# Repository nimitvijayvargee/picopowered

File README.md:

# picopowered
A simple microcontroller built around the RP2040.

# Changelog (V3)
- Redesigned board layout
- Doubled headers
- Dip switches and SD card slot connected to GP13-15 and GP16-19+29 respectively
- Better power system and circuit design

# Changelog (V2)
- Replaced 2020 Neopixel with more available 5050 footprint.
- Fixed seperation between 1v1 and 3v3 power planes.
- Better positioning and tracing of the components to improve overall signal integrity.
- Added a regular LED to keep it somewhat compatible with regular Pico SDK Code.
- Modified USB C port to be THT Mounted rather than completely SMD.
- Moved GPIO 29 from VSYS Sense to an exposed pad on the bottom side of the PCB.

# Featureset
| **Stat**         | **Raspberry Pi Pico 1** | **Picopowered V1-RP2040** |
|------------------|-------------------------|---------------------------|
| Flash            | 2MB                     | 16MB                      |
| Reset Button     | No                      | Yes                       |
| LED              | Yes (1 Color)           | Yes (RGB Neopixel)        |
| User GPIO Button | No                      | Yes                       |
| USB Type         | Micro-B                 | C                         |

# Disadvantages
- Linear regulator requuires minimum of 3.3 Volts, unlike Pico's buck boost converter which can be powered by 1.8 Volts.
- ~~No ADC_VREF (connected to GND instead) because the power by linear regulator is filtered already.~~ ADC VREF now works with picopowered V2 and V3
- No Power Mode selection (stems from power supply used)

Most of the disadvantages occur only due to the Pico's superior power supply system, but the system on the PicoPowered board is more filtered and smooth.

# BOM
| **Part**         | **Cost (USD)**          |
|------------------|-------------------------|
| PCB + Assembly   | 120                     |
| Solder Wire      | 3                       |
| Headers          | 3                       |

For parts specific BOM, check picopowered.csv in /Production/

# Gallery
## V3 (Latest)

## V2

## V1

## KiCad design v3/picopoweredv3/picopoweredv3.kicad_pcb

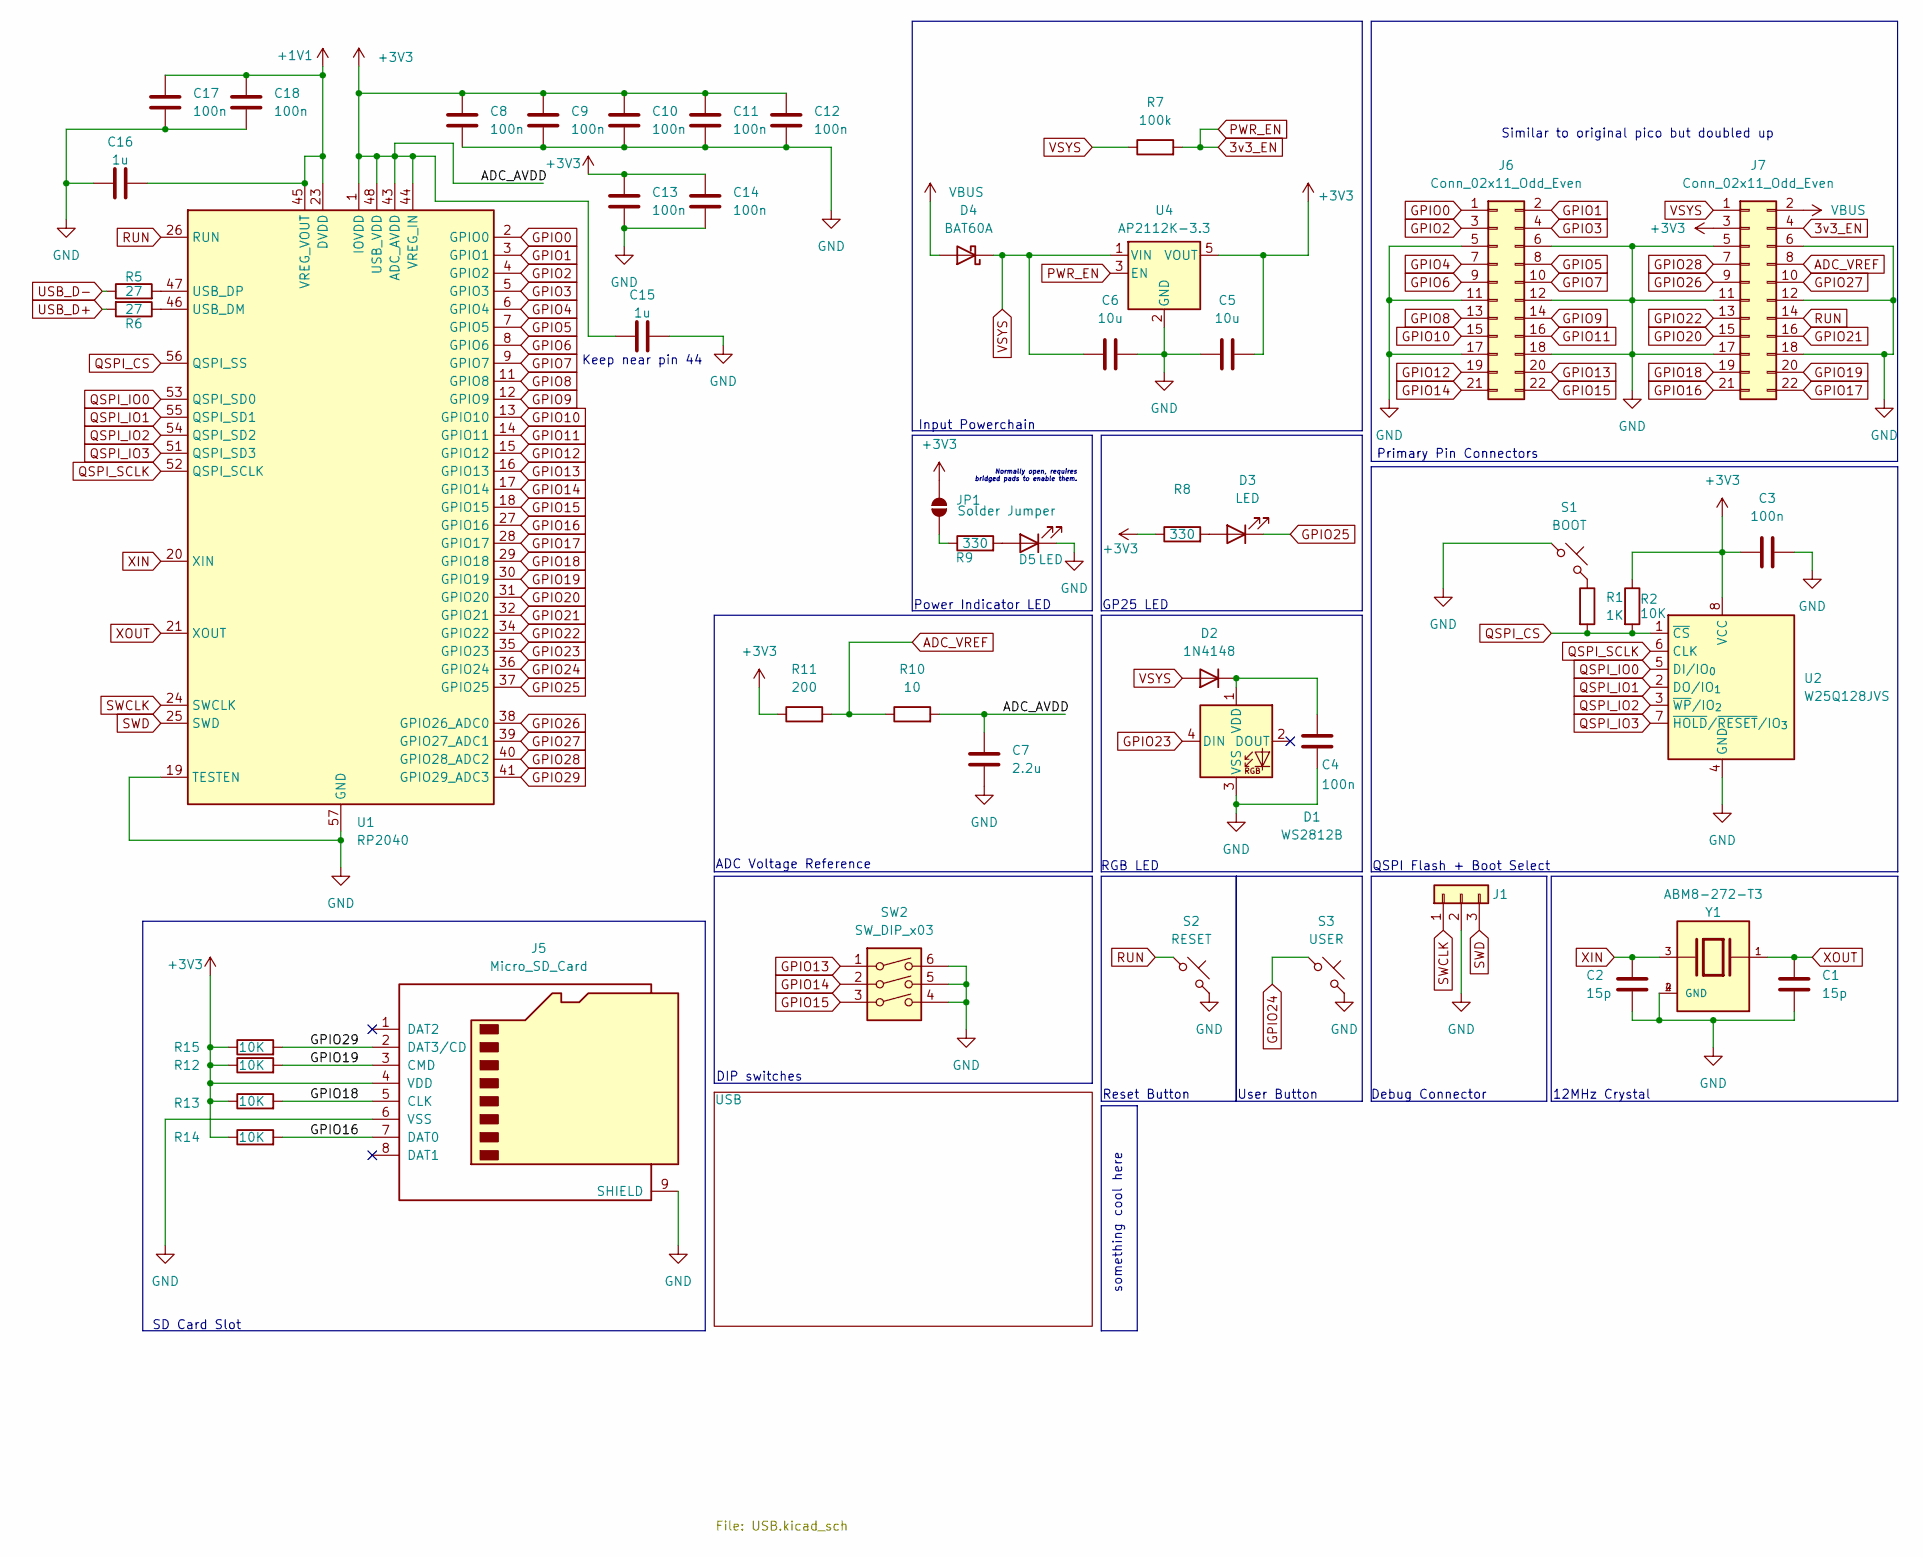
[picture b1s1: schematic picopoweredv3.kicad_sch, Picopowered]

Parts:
C1, C2: 15p; C_0402_1005Metric
C3, C4, C8, C9, C10, C11, C12, C13, C14, C17, C18: 100n; C_0402_1005Metric
C5, C6: 10u; C_0402_1005Metric
C7: 2.2u; C_0402_1005Metric
C15, C16: 1u; C_0402_1005Metric
D1: WS2812B; LED_WS2812B_PLCC4_5.0x5.0mm_P3.2mm
D2: 1N4148; D_SOD-123
D3, D5: LED; LED_0603_1608Metric
D4: BAT60A; D_SOD-323
J1: Conn_01x03; PinHeader_1x03_P2.54mm_Vertical
J5: Micro_SD_Card; Micro_SD_READER
J6, J7: Conn_02x11_Odd_Even; PinHeader_2x11_P2.54mm_Vertical
JP1: Solder Jumper; SolderJumper-2_P1.3mm_Open_TrianglePad1.0x1.5mm
R1: 1K; R_0402_1005Metric
R2, R12, R13, R14, R15: 10K; R_0402_1005Metric
R5, R6: 27; R_0402_1005Metric
R7: 100k; R_0402_1005Metric
R8, R9: 330; R_0402_1005Metric
R10: 10; R_0402_1005Metric
R11: 200; R_0402_1005Metric
S1: BOOT; SW_SPST_B3U-1000P
S2: RESET; SW_SPST_B3U-1000P
S3: USER; SW_SPST_B3U-1000P
SW2: SW_DIP_x03; SW_DIP_SPSTx03_Slide_6.7x9.18mm_W7.62mm_P2.54mm_LowProfile
U1: RP2040; QFN-56-1EP_7x7mm_P0.4mm_EP3.2x3.2mm
U2: W25Q128JVS; SOIC-8_5.3x5.3mm_P1.27mm
U4: AP2112K-3.3; SOT-23-5
Y1: ABM8-272-T3; XTAL_ABM8-272-T3; PARTREV 07-29-20

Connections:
3v3_EN: J7.4, R7.2, U4.3 (EN)
+1V1: C16.1, C17.1, C18.1, U1.23 (DVDD), U1.45 (VREG_VOUT), U1.50 (DVDD)
+3V3: C3.1, C5.1, C7.1, C8.1, C9.1, C10.1, C11.1, C12.1, C13.1, C14.1, C15.1, J5.4 (VDD), J7.3, JP1.2 (B), R2.1, R8.1, R10.2, R11.1, R12.1, R13.1, R14.1, R15.1, U1.1 (IOVDD), U1.10 (IOVDD), U1.22 (IOVDD), U1.33 (IOVDD), U1.42 (IOVDD), U1.43 (ADC_AVDD), U1.44 (VREG_IN), U1.48 (USB_VDD), U1.49 (IOVDD), U2.8 (VCC), U4.5 (VOUT)
ADC_VREF: J7.8, R10.1, R11.2
GND: C1.2, C2.2, C3.2, C4.1, C5.2, C6.2, C7.2, C8.2, C9.2, C10.2, C11.2, C12.2, C13.2, C14.2, C15.2, C16.2, C17.2, C18.2, D1.3 (VSS), D5.1 (K), J1.2, J5.6 (VSS), J5.9 (SHIELD), J6.5, J6.6, J6.11, J6.12, J6.17, J6.18, J7.5, J7.6, J7.11, J7.12, J7.17, J7.18, S1.1, S2.2, S3.2, SW2.4, SW2.5, SW2.6, U1.19 (TESTEN), U1.57 (GND), U2.4 (GND), U4.2 (GND), Y1.2 (GND), Y1.4 (GND); also elsewhere on the board
GPIO0: J6.1, U1.2 (GPIO0)
GPIO1: J6.2, U1.3 (GPIO1)
GPIO2: J6.3, U1.4 (GPIO2)
GPIO3: J6.4, U1.5 (GPIO3)
GPIO4: J6.7, U1.6 (GPIO4)
GPIO5: J6.8, U1.7 (GPIO5)
GPIO6: J6.9, U1.8 (GPIO6)
GPIO7: J6.10, U1.9 (GPIO7)
GPIO8: J6.13, U1.11 (GPIO8)
GPIO9: J6.14, U1.12 (GPIO9)
GPIO10: J6.15, U1.13 (GPIO10)
GPIO11: J6.16, U1.14 (GPIO11)
GPIO12: J6.19, U1.15 (GPIO12)
GPIO13: J6.20, SW2.1, U1.16 (GPIO13)
GPIO14: J6.21, SW2.2, U1.17 (GPIO14)
GPIO15: J6.22, SW2.3, U1.18 (GPIO15)
GPIO16: J5.7 (DAT0), J7.21, R14.2, U1.27 (GPIO16)
GPIO17: J7.22, U1.28 (GPIO17)
GPIO18: J5.5 (CLK), J7.19, R13.2, U1.29 (GPIO18)
GPIO19: J5.3 (CMD), J7.20, R12.2, U1.30 (GPIO19)
GPIO20: J7.15, U1.31 (GPIO20)
GPIO21: J7.16, U1.32 (GPIO21)
GPIO22: J7.13, U1.34 (GPIO22)
GPIO23: D1.4 (DIN), U1.35 (GPIO23)
GPIO24: S3.1, U1.36 (GPIO24)
GPIO25: D3.1 (K), U1.37 (GPIO25)
GPIO26: J7.9, U1.38 (GPIO26_ADC0)
GPIO27: J7.10, U1.39 (GPIO27_ADC1)
GPIO28: J7.7, U1.40 (GPIO28_ADC2)
GPIO29: J5.2 (DAT3/CD), R15.2, U1.41 (GPIO29_ADC3)
unnamed: C4.2, D1.1 (VDD), D2.1 (K)
unnamed: D3.2 (A), R8.2
unnamed: D5.2 (A), R9.2
unnamed: JP1.1 (A), R9.1
unnamed: R1.1, S1.2
unnamed: R6.1, U1.46 (USB_DM)
unnamed: R5.2, U1.47 (USB_DP)
QSPI_CS: R1.2, R2.2, U1.56 (QSPI_SS), U2.1 (~CS)
QSPI_IO0: U1.53 (QSPI_SD0), U2.5 (DI/IO_{0})
QSPI_IO1: U1.55 (QSPI_SD1), U2.2 (DO/IO_{1})
QSPI_IO2: U1.54 (QSPI_SD2), U2.3 (~WP/IO_{2})
QSPI_IO3: U1.51 (QSPI_SD3), U2.7 (~HOLD/~RESET/IO_{3})
QSPI_SCLK: U1.52 (QSPI_SCLK), U2.6 (CLK)
RUN: J7.14, S2.1, U1.26 (RUN)
SWCLK: J1.1, U1.24 (SWCLK)
SWD: J1.3, U1.25 (SWD)
USB_D+: R6.2; also elsewhere on the board
USB_D-: R5.1; also elsewhere on the board
VBUS: D4.2 (A), J7.2; also elsewhere on the board
VSYS: C6.1, D2.2 (A), D4.1 (K), J7.1, R7.1, U4.1 (VIN)
XIN: C2.1, U1.20 (XIN), Y1.3
XOUT: C1.1, U1.21 (XOUT), Y1.1

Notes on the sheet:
Similar to original pico but doubled up
DIP switches
ADC Voltage Reference
Normally open, requires bridged pads to enable them.
GP25 LED
User Button
QSPI Flash + Boot Select
Primary Pin Connectors
something cool here
RGB LED
Input Powerchain
Debug Connector
12MHz Crystal
Keep near pin 44
SD Card Slot
Power Indicator LED
Reset Button

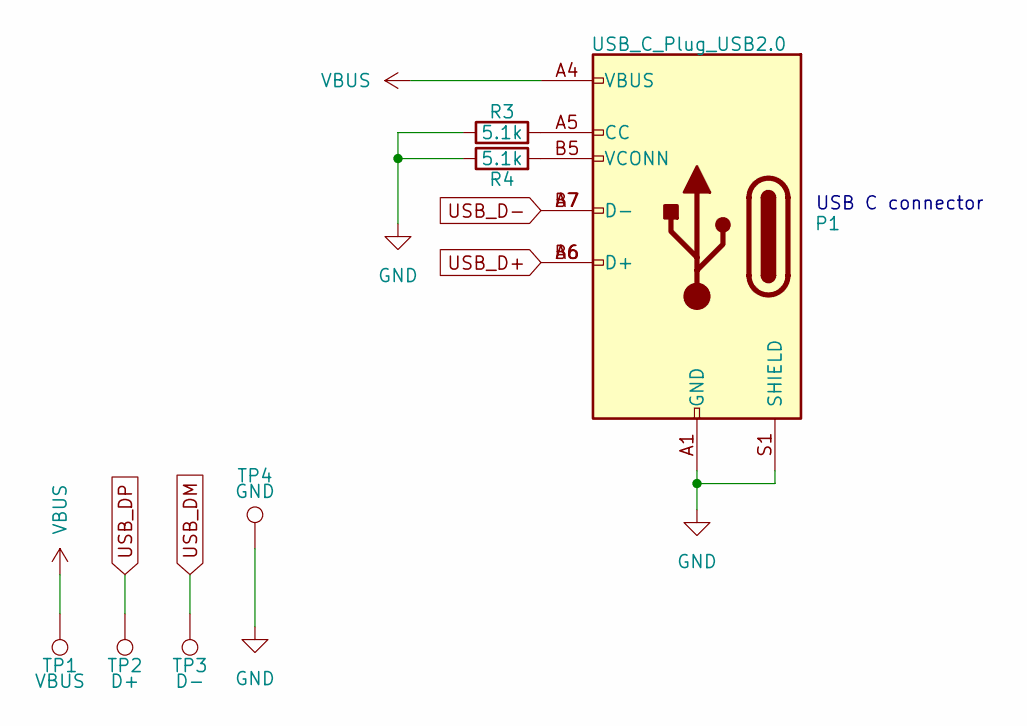
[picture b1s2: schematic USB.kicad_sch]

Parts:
P1: USB_C_Plug_USB2.0; USB_C_Receptacle_GCT_USB4105-xx-A_16P_TopMnt_Horizontal
R3, R4: 5.1k; R_0402_1005Metric
TP1: VBUS; TestPoint_Pad_1.0x1.0mm
TP2: D+; TestPoint_Pad_1.0x1.0mm
TP3: D-; TestPoint_Pad_1.0x1.0mm
TP4: GND; TestPoint_Pad_1.0x1.0mm

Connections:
GND: P1.A1 (GND), P1.A12 (GND), P1.B1 (GND), P1.B12 (GND), P1.S1 (SHIELD), R3.1, R4.1, TP4.1; also elsewhere on the board
unnamed: P1.A5 (CC), R3.2
unnamed: P1.B5 (VCONN), R4.2
USB_D+: P1.A6 (D+), P1.B6 (D+); also elsewhere on the board
USB_D-: P1.A7 (D-), P1.B7 (D-); also elsewhere on the board
VBUS: P1.A4 (VBUS), P1.A9 (VBUS), P1.B4 (VBUS), P1.B9 (VBUS), TP1.1; also elsewhere on the board

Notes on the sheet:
USB C connector

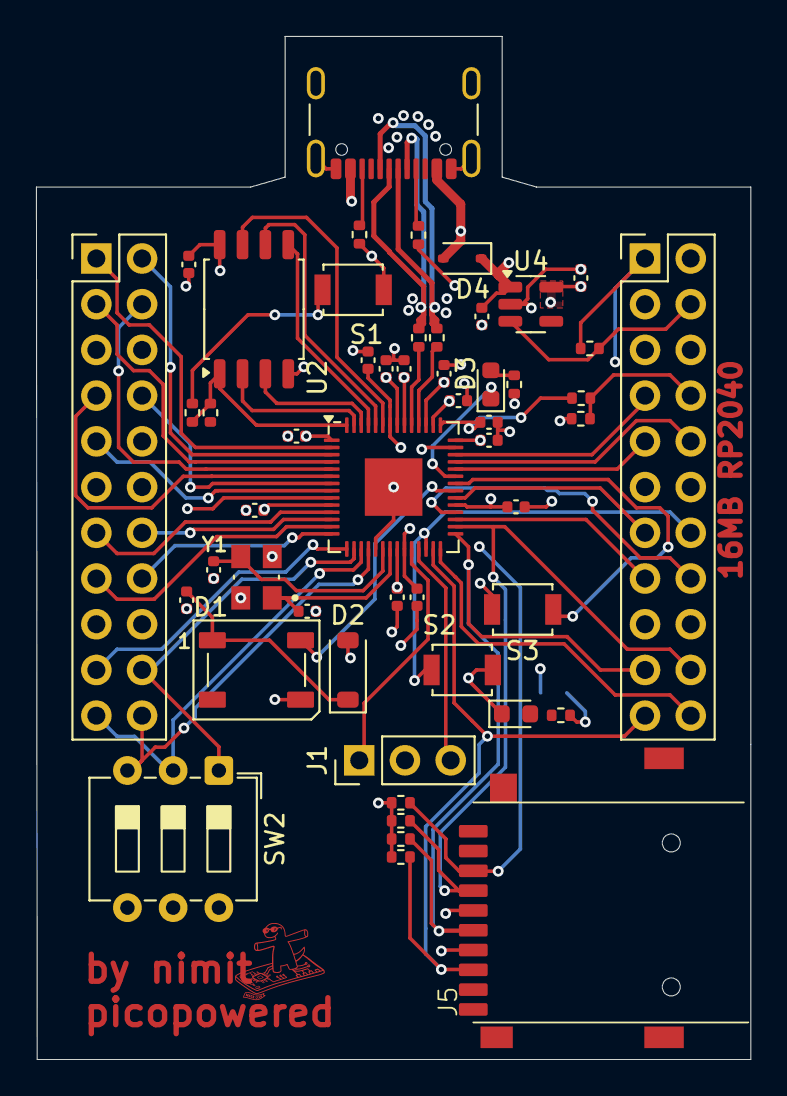
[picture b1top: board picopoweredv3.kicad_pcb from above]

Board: 4 copper layers, 39.7 x 56.8 mm, 52 parts (1 on the bottom side), 59 nets.

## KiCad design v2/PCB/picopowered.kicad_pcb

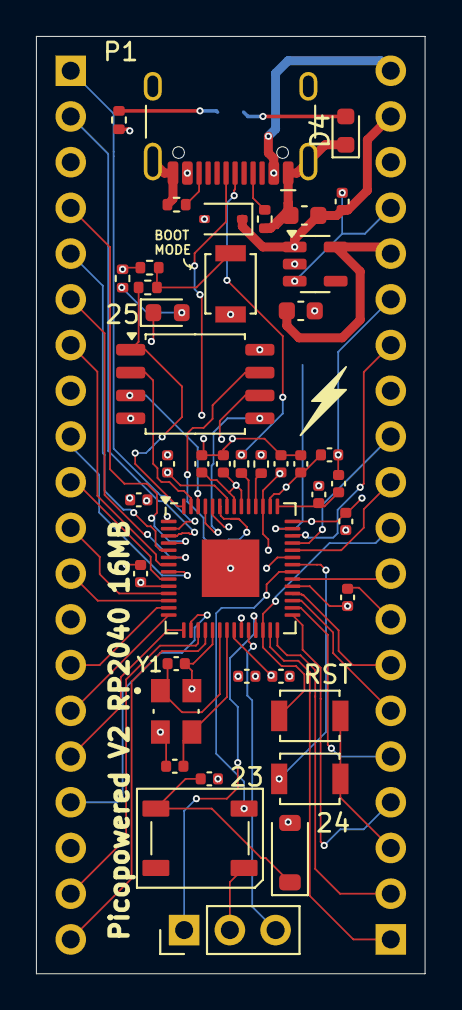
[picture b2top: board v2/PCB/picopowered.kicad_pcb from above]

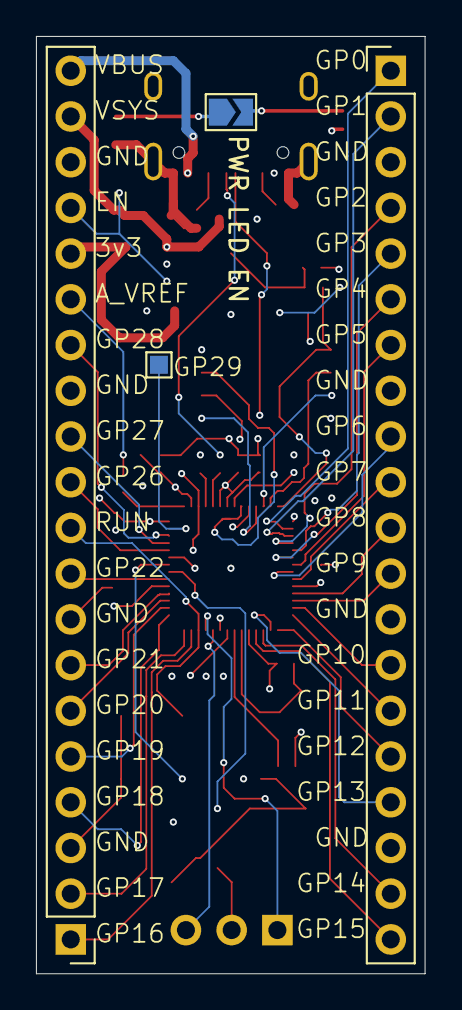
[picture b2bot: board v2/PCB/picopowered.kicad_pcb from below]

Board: 4 copper layers, 21.6 x 52.1 mm, 46 parts (4 on the bottom side), 60 nets.

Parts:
24: USER_BUTTON; SW_SPST_B3U-1000P
25: LED; LED_0603_1608Metric
BOOT: BOOT_SELECT; SW_SPST_B3U-1000P
C1, C2: 15p; C_0402_1005Metric
C3, C4, C5, C6, C7, C8, C9, C10, C10#2, C13: 100n; C_0402_1005Metric
C11, C12, C16: 2.2u; C_0402_1005Metric
C14: 10u; C_0603_1608Metric
C15: 22u; C_0603_1608Metric
D1: WS2812B; LED_WS2812B_PLCC4_5.0x5.0mm_P3.2mm
D2: 1N4148; D_SOD-123
D4: LED; LED_0603_1608Metric
D5: BAT60A; D_SOD-323
J1: Conn_01x03; PinHeader_1x03_P2.54mm_Vertical
J2, J3: Conn_01x20; PinHeader_1x20_P2.54mm_Vertical
P1: USB_C_Plug_USB2.0; USB_C_Receptacle_HCTL_HC-TYPE-C-16P-01A
PWR LED EN: SolderJumper_2_Open; SolderJumper-2_P1.3mm_Open_TrianglePad1.0x1.5mm
Picopowered V2 RP2040 16MB: RP2040; QFN-56-1EP_7x7mm_P0.4mm_EP3.2x3.2mm
R1, R2: 27; R_0402_1005Metric
R3: 1k; R_0402_1005Metric
R4: 10k; R_0402_1005Metric
R5, R6: 5.1k; R_0402_1005Metric
R7, R8: 330; R_0402_1005Metric
R9: 10; C_0402_1005Metric
R10: 200; C_0402_1005Metric
R11: 100K; C_0402_1005Metric
RST: Keyswitch; SW_SPST_B3U-1000P
TP1: GP29; TestPoint_Pad_1.0x1.0mm
U2: W25Q128JVS; SOIC-8_5.3x5.3mm_P1.27mm
U4: AP2112K-3.3; SOT-23-5
Y1: ABM8-272-T3; XTAL_ABM8-272-T3

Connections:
3v3_EN: J3.17, R11.1, U4.3 (EN)
+1V1: C3.1, C4.1, C12.1, Picopowered V2 RP2040 16MB.23 (DVDD), Picopowered V2 RP2040 16MB.45 (VREG_VOUT), Picopowered V2 RP2040 16MB.50 (DVDD)
+3V3: C5.1, C6.1, C7.1, C8.1, C9.1, C10.1, C10#2.1, C11.1, C15.2, J3.16, Picopowered V2 RP2040 16MB.1 (IOVDD), Picopowered V2 RP2040 16MB.10 (IOVDD), Picopowered V2 RP2040 16MB.22 (IOVDD), Picopowered V2 RP2040 16MB.33 (IOVDD), Picopowered V2 RP2040 16MB.42 (IOVDD), Picopowered V2 RP2040 16MB.44 (VREG_IN), Picopowered V2 RP2040 16MB.48 (USB_VDD), Picopowered V2 RP2040 16MB.49 (IOVDD), R4.2, R7.2, R8.2, R10.1, U2.8 (VCC), U4.5 (VOUT)
ADC_AVDD: C16.1, Picopowered V2 RP2040 16MB.43 (ADC_AVDD), R9.2
ADC_VREF: J3.15, R9.1, R10.2
GND: 24.2, BOOT.1, C1.1, C2.1, C3.2, C4.2, C5.2, C6.2, C7.2, C8.2, C9.2, C10.2, C10#2.2, C11.2, C12.2, C13.2, C14.1, C15.1, C16.2, D1.3 (VSS), D4.1 (K), J1.2, J2.3, J2.8, J2.13, J2.18, J3.3, J3.8, J3.13, J3.18, P1.A1 (GND), P1.A12 (GND), P1.B1 (GND), P1.B12 (GND), P1.S1 (SHIELD), Picopowered V2 RP2040 16MB.19 (TESTEN), Picopowered V2 RP2040 16MB.57 (GND), R5.2, R6.2, RST.2, U2.4 (GND), U4.2 (GND), Y1.2 (GND), Y1.4 (GND)
GPIO0: J2.1, Picopowered V2 RP2040 16MB.2 (GPIO0)
GPIO1: J2.2, Picopowered V2 RP2040 16MB.3 (GPIO1)
GPIO2: J2.4, Picopowered V2 RP2040 16MB.4 (GPIO2)
GPIO3: J2.5, Picopowered V2 RP2040 16MB.5 (GPIO3)
GPIO4: J2.6, Picopowered V2 RP2040 16MB.6 (GPIO4)
GPIO5: J2.7, Picopowered V2 RP2040 16MB.7 (GPIO5)
GPIO6: J2.9, Picopowered V2 RP2040 16MB.8 (GPIO6)
GPIO7: J2.10, Picopowered V2 RP2040 16MB.9 (GPIO7)
GPIO8: J2.11, Picopowered V2 RP2040 16MB.11 (GPIO8)
GPIO9: J2.12, Picopowered V2 RP2040 16MB.12 (GPIO9)
GPIO10: J2.14, Picopowered V2 RP2040 16MB.13 (GPIO10)
GPIO11: J2.15, Picopowered V2 RP2040 16MB.14 (GPIO11)
GPIO12: J2.16, Picopowered V2 RP2040 16MB.15 (GPIO12)
GPIO13: J2.17, Picopowered V2 RP2040 16MB.16 (GPIO13)
GPIO14: J2.19, Picopowered V2 RP2040 16MB.17 (GPIO14)
GPIO15: J2.20, Picopowered V2 RP2040 16MB.18 (GPIO15)
GPIO16: J3.1, Picopowered V2 RP2040 16MB.27 (GPIO16)
GPIO17: J3.2, Picopowered V2 RP2040 16MB.28 (GPIO17)
GPIO18: J3.4, Picopowered V2 RP2040 16MB.29 (GPIO18)
GPIO19: J3.5, Picopowered V2 RP2040 16MB.30 (GPIO19)
GPIO20: J3.6, Picopowered V2 RP2040 16MB.31 (GPIO20)
GPIO21: J3.7, Picopowered V2 RP2040 16MB.32 (GPIO21)
GPIO22: J3.9, Picopowered V2 RP2040 16MB.34 (GPIO22)
GPIO23: D1.4 (DIN), Picopowered V2 RP2040 16MB.35 (GPIO23)
GPIO24: 24.1, Picopowered V2 RP2040 16MB.36 (GPIO24)
GPIO25: 25.1 (K), Picopowered V2 RP2040 16MB.37 (GPIO25)
GPIO26: J3.11, Picopowered V2 RP2040 16MB.38 (GPIO26_ADC0)
GPIO27: J3.12, Picopowered V2 RP2040 16MB.39 (GPIO27_ADC1)
GPIO28: J3.14, Picopowered V2 RP2040 16MB.40 (GPIO28_ADC2)
GPIO29: Picopowered V2 RP2040 16MB.41 (GPIO29_ADC3), TP1.1
unnamed: C13.1, D1.1 (VDD), D2.1 (K)
unnamed: 25.2 (A), R7.1
unnamed: D4.2 (A), PWR LED EN.1 (A)
unnamed: J1.1, Picopowered V2 RP2040 16MB.25 (SWD)
unnamed: J1.3, Picopowered V2 RP2040 16MB.24 (SWCLK)
unnamed: PWR LED EN.2 (B), R8.1
unnamed: P1.A5 (CC), R5.1
unnamed: P1.B5 (VCONN), R6.1
unnamed: BOOT.2, R3.1, R4.1
unnamed: Picopowered V2 RP2040 16MB.46 (USB_DM), R2.2
unnamed: Picopowered V2 RP2040 16MB.47 (USB_DP), R1.2
unnamed: C1.2, Picopowered V2 RP2040 16MB.20 (XIN), Y1.1
unnamed: C2.2, Picopowered V2 RP2040 16MB.21 (XOUT), Y1.3
QSPI_SCLK: Picopowered V2 RP2040 16MB.52 (QSPI_SCLK), U2.6 (CLK)
QSPI_SD0: Picopowered V2 RP2040 16MB.53 (QSPI_SD0), U2.5 (DI/IO_{0})
QSPI_SD1: Picopowered V2 RP2040 16MB.55 (QSPI_SD1), U2.2 (DO/IO_{1})
QSPI_SD2: Picopowered V2 RP2040 16MB.54 (QSPI_SD2), U2.3 (~WP/IO_{2})
QSPI_SD3: Picopowered V2 RP2040 16MB.51 (QSPI_SD3), U2.7 (~HOLD/~RESET/IO_{3})
QSPI_SS: Picopowered V2 RP2040 16MB.56 (QSPI_SS), R3.2, U2.1 (~CS)
RUN: J3.10, Picopowered V2 RP2040 16MB.26 (RUN), RST.1
USB_D+: P1.A6 (D+), R1.1
USB_D-: P1.A7 (D-), R2.1
VBUS: D5.2 (A), J3.20, P1.A4 (VBUS), P1.A9 (VBUS), P1.B4 (VBUS), P1.B9 (VBUS)
VSYS: C14.2, D2.2 (A), D5.1 (K), J3.19, R11.2, U4.1 (VIN)

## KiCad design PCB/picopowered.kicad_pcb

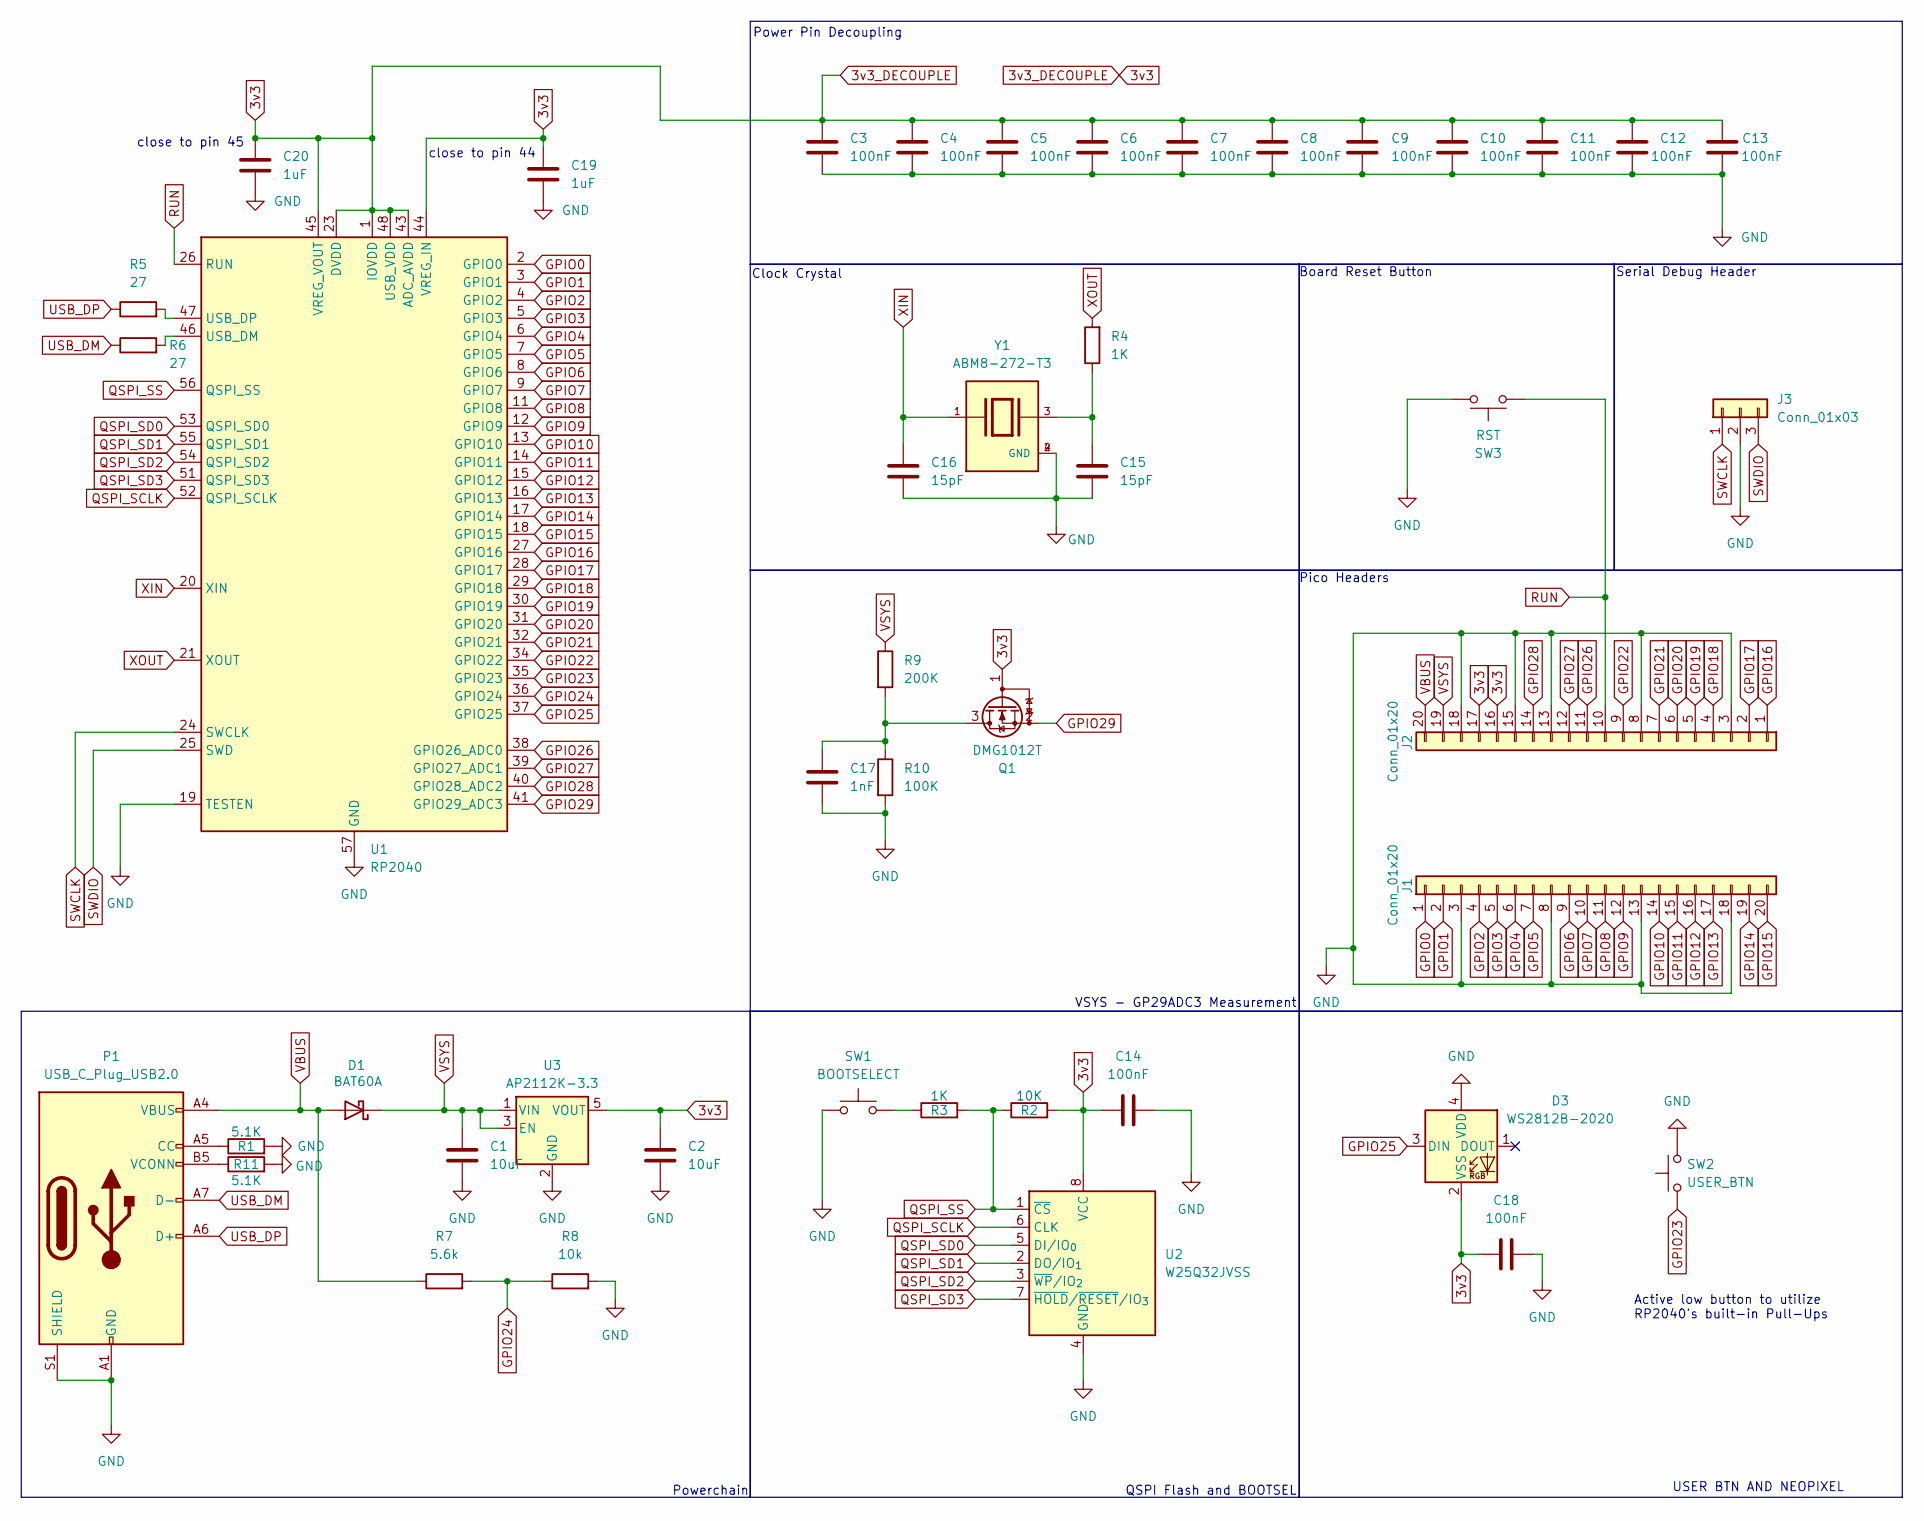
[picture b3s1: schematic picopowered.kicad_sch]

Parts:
C1, C2: 10uF; C_0402_1005Metric
C3, C4, C5, C6, C7, C8, C9, C10, C11, C12, C13, C14, C18: 100nF; C_0402_1005Metric
C15, C16: 15pF; C_0402_1005Metric
C17: 1nF; C_0402_1005Metric
C19, C20: 1uF; C_0402_1005Metric
D1: BAT60A; D_SOD-123
D3: WS2812B-2020; LED_WS2812B-2020_PLCC4_2.0x2.0mm
J1, J2: Conn_01x20; PinHeader_1x20_P2.54mm_Vertical
J3: Conn_01x03; PinHeader_1x03_P2.54mm_Vertical
P1: USB_C_Plug_USB2.0; USB_C_Receptacle_GCT_USB4110
Q1: DMG1012T; SOT-523
R1, R11: 5.1K; R_0402_1005Metric
R2: 10K; R_0402_1005Metric
R3, R4: 1K; R_0402_1005Metric
R5, R6: 27; R_0402_1005Metric
R7: 5.6k; R_0402_1005Metric
R8: 10k; R_0402_1005Metric
R9: 200K; R_0402_1005Metric
R10: 100K; R_0402_1005Metric
SW1: BOOTSELECT; SW_SPST_B3U-1000P
SW2: USER_BTN; SW_SPST_B3U-1000P
SW3: RST; SW_SPST_B3U-1000P
U1: RP2040; QFN-56-1EP_7x7mm_P0.4mm_EP3.2x3.2mm
U2: W25Q32JVSS; SOIC-8_5.3x5.3mm_P1.27mm
U3: AP2112K-3.3; SOT-23-5
Y1: ABM8-272-T3; Crystal_SMD_Abracon_ABM8G-4Pin_3.2x2.5mm; PARTREV 07-29-20

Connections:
3v3: C2.1, C3.1, C4.1, C5.1, C6.1, C7.1, C8.1, C9.1, C10.1, C11.1, C12.1, C13.1, C14.1, C18.1, C19.1, C20.1, D3.2 (VSS), J2.16, J2.17, Q1.1 (G), R2.2, U1.1 (IOVDD), U1.10 (IOVDD), U1.22 (IOVDD), U1.23 (DVDD), U1.33 (IOVDD), U1.42 (IOVDD), U1.43 (ADC_AVDD), U1.44 (VREG_IN), U1.45 (VREG_VOUT), U1.48 (USB_VDD), U1.49 (IOVDD), U1.50 (DVDD), U2.8 (VCC), U3.5 (VOUT)
GND: C1.2, C2.2, C3.2, C4.2, C5.2, C6.2, C7.2, C8.2, C9.2, C10.2, C11.2, C12.2, C13.2, C14.2, C15.1, C16.1, C17.2, C18.2, C19.2, C20.2, D3.4 (VDD), J1.3, J1.8, J1.13, J1.18, J2.3, J2.8, J2.13, J2.15, J2.18, J3.2, P1.A1 (GND), P1.A12 (GND), P1.B1 (GND), P1.B12 (GND), P1.S1 (SHIELD), R1.2, R8.2, R10.2, R11.2, SW1.1, SW2.2, SW3.1, U1.19 (TESTEN), U1.57 (GND), U2.4 (GND), U3.2 (GND), Y1.2 (GND), Y1.4 (GND)
GPIO0: J1.1, U1.2 (GPIO0)
GPIO1: J1.2, U1.3 (GPIO1)
GPIO2: J1.4, U1.4 (GPIO2)
GPIO3: J1.5, U1.5 (GPIO3)
GPIO4: J1.6, U1.6 (GPIO4)
GPIO5: J1.7, U1.7 (GPIO5)
GPIO6: J1.9, U1.8 (GPIO6)
GPIO7: J1.10, U1.9 (GPIO7)
GPIO8: J1.11, U1.11 (GPIO8)
GPIO9: J1.12, U1.12 (GPIO9)
GPIO10: J1.14, U1.13 (GPIO10)
GPIO11: J1.15, U1.14 (GPIO11)
GPIO12: J1.16, U1.15 (GPIO12)
GPIO13: J1.17, U1.16 (GPIO13)
GPIO14: J1.19, U1.17 (GPIO14)
GPIO15: J1.20, U1.18 (GPIO15)
GPIO16: J2.1, U1.27 (GPIO16)
GPIO17: J2.2, U1.28 (GPIO17)
GPIO18: J2.4, U1.29 (GPIO18)
GPIO19: J2.5, U1.30 (GPIO19)
GPIO20: J2.6, U1.31 (GPIO20)
GPIO21: J2.7, U1.32 (GPIO21)
GPIO22: J2.9, U1.34 (GPIO22)
GPIO23: SW2.1, U1.35 (GPIO23)
GPIO24: R7.2, R8.1, U1.36 (GPIO24)
GPIO25: D3.3 (DIN), U1.37 (GPIO25)
GPIO26: J2.11, U1.38 (GPIO26_ADC0)
GPIO27: J2.12, U1.39 (GPIO27_ADC1)
GPIO28: J2.14, U1.40 (GPIO28_ADC2)
GPIO29: Q1.2 (S), U1.41 (GPIO29_ADC3)
unnamed: C15.2, R4.1, Y1.3
unnamed: P1.A5 (CC), R1.1
unnamed: P1.B5 (VCONN), R11.1
unnamed: C17.1, Q1.3 (D), R9.2, R10.1
unnamed: R3.1, SW1.2
unnamed: R6.2, U1.46 (USB_DM)
unnamed: R5.2, U1.47 (USB_DP)
QSPI_SCLK: U1.52 (QSPI_SCLK), U2.6 (CLK)
QSPI_SD0: U1.53 (QSPI_SD0), U2.5 (DI/IO_{0})
QSPI_SD1: U1.55 (QSPI_SD1), U2.2 (DO/IO_{1})
QSPI_SD2: U1.54 (QSPI_SD2), U2.3 (~WP/IO_{2})
QSPI_SD3: U1.51 (QSPI_SD3), U2.7 (~HOLD/~RESET/IO_{3})
QSPI_SS: R2.1, R3.2, U1.56 (QSPI_SS), U2.1 (~CS)
RUN: J2.10, SW3.2, U1.26 (RUN)
SWCLK: J3.1, U1.24 (SWCLK)
SWDIO: J3.3, U1.25 (SWD)
USB_DM: P1.A7 (D-), R6.1
USB_DP: P1.A6 (D+), R5.1
VBUS: D1.2 (A), J2.20, P1.A4 (VBUS), P1.A9 (VBUS), P1.B4 (VBUS), P1.B9 (VBUS), R7.1
VSYS: C1.1, D1.1 (K), J2.19, R9.1, U3.1 (VIN), U3.3 (EN)
XIN: C16.2, U1.20 (XIN), Y1.1
XOUT: R4.2, U1.21 (XOUT)

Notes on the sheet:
USER BTN AND NEOPIXEL
Serial Debug Header
Pico Headers
Active low button to utilize RP2040's built-in Pull-Ups
close to pin 45
Power Pin Decoupling
Board Reset Button
Powerchain
VSYS - GP29ADC3 Measurement
QSPI Flash and BOOTSEL
Clock Crystal
close to pin 44

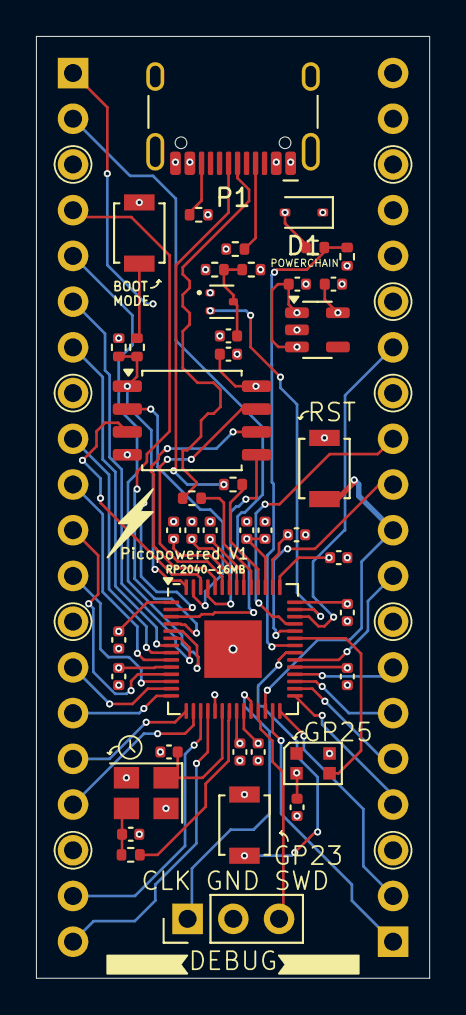
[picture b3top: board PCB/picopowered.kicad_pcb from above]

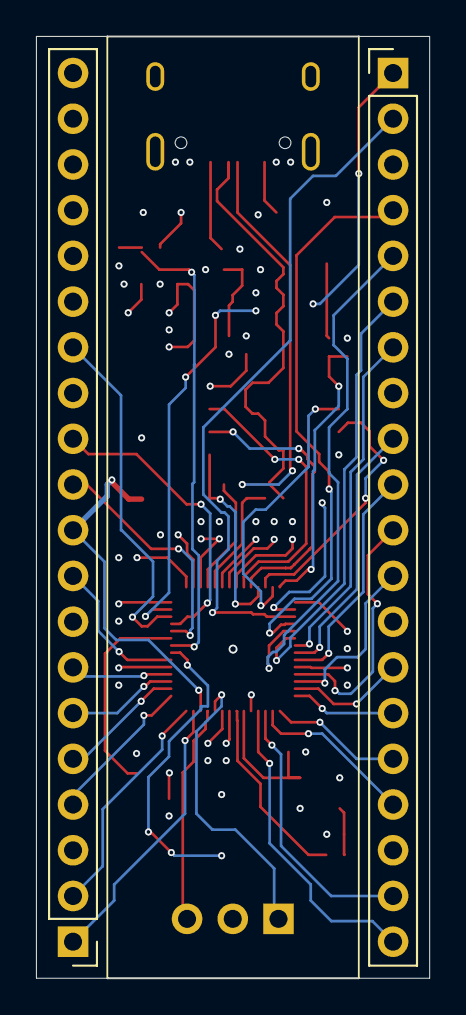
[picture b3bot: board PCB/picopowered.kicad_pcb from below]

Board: 4 copper layers, 21.8 x 52.3 mm, 45 parts (2 on the bottom side), 54 nets.

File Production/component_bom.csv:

Reference,Qty,Value,DNP,Exclude from BOM,Exclude from Board,Footprint,JLCPCB Part
"C1,C2",2,10uF,,,,Capacitor_SMD:C_0402_1005Metric,C315248
"C3,C4,C5,C6,C7,C8,C9,C10,C11,C12,C13,C14,C18",13,100nF,,,,Capacitor_SMD:C_0402_1005Metric,C77020
"C15,C16",2,15pF,,,,Capacitor_SMD:C_0402_1005Metric,C106997
C17,1,1nF,,,,Capacitor_SMD:C_0402_1005Metric,C106205
"C19,C20",2,1uF,,,,Capacitor_SMD:C_0402_1005Metric,C29266
D1,1,BAT60A,,,,Diode_SMD:D_SOD-123,C5355496
D3,1,WS2812B-2020,,,,LED_SMD:LED_WS2812B-2020_PLCC4_2.0x2.0mm,C5349955
P1,1,USB_C_Plug_USB2.0,,,,Connector_USB:USB_C_Receptacle,C2765186
Q1,1,DMG1012T,,,,Package_TO_SOT_SMD:SOT-523,C2830301
"R1,R11",2,5.1K,,,,Resistor_SMD:R_0402_1005Metric,C105872
R2,1,10K,,,,Resistor_SMD:R_0402_1005Metric,C60490
"R3,R4",2,1K,,,,Resistor_SMD:R_0402_1005Metric,C106235
"R5,R6",2,27,,,,Resistor_SMD:R_0402_1005Metric,C138021
R7,1,5.6k,,,,Resistor_SMD:R_0402_1005Metric,C163457
R8,1,10k,,,,Resistor_SMD:R_0402_1005Metric,C60490
R9,1,200K,,,,Resistor_SMD:R_0402_1005Metric,C114763
R10,1,100K,,,,Resistor_SMD:R_0402_1005Metric,C60491
SW1,1,BOOTSELECT,,,,Button_Switch_SMD:SW_SPST_B3U-1000P,C231329
SW2,1,USER_BTN,,,,Button_Switch_SMD:SW_SPST_B3U-1000P,C231329
SW3,1,RST,,,,Button_Switch_SMD:SW_SPST_B3U-1000P,C231329
U1,1,RP2040,,,,Package_DFN_QFN:QFN-56-1EP_7x7mm_P0.4mm_EP3.2x3.2mm,C2040
U2,1,W25Q32JVSS,,,,Package_SO:SOIC-8_5.3x5.3mm_P1.27mm,C97521
U3,1,AP2112K-3.3,,,,Package_TO_SOT_SMD:SOT-23-5,C23380830
Y1,1,ABM8-272-T3,,,,Crystal:Crystal_SMD_Abracon_ABM8G-4Pin_3.2x2.5mm,C20625731
,,,,,,,

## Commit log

2025-06-19 line breaks are a powerful tool
2025-06-22 Clarify journal
2025-06-25 Submission Ready
2025-06-25 Added Images
2025-06-26 Minor Changes
2025-06-26 Minor trace changes and updated BOM
2025-08-15 Add version 2
2025-08-16 Fixed Readme for V2
2025-09-10 Version 3!
2025-09-10 Rename PCB folder and update README
